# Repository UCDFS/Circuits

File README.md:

# UCDFS Circuits Repository

Welcome to the University College Dublin Formula Student (UCDFS) KiCad circuits repository! This is the central location for all our electronic circuit designs, schematics, and PCB layouts.

## About

This repository contains KiCad project files for various electronic circuits used in our Formula Student vehicle and projects. All designs are created using KiCad, an open-source electronic design automation (EDA) suite.

## Getting Started

1. **Clone this repository:**
   ```bash
   git clone https://github.com/UCDFS/Circuits.git
   cd Circuits
   ```

2. **Open a project in KiCad:**
   - Launch KiCad
   - Open the `.kicad_pro` file for the project you want to work on
   - The schematic (`.kicad_sch`) and PCB layout (`.kicad_pcb`) will be accessible from the project manager

3. **View/Edit Schematics:**
   - Click "Schematic Editor" in KiCad's main window
   - Or directly open the `.kicad_sch` file

4. **View/Edit PCB Layout:**
   - Click "PCB Editor" in KiCad's main window
   - Or directly open the `.kicad_pcb` file

## Repository Structure

```
├── README.md                     # This file
├── .gitignore                    # Git ignore rules for KiCad projects
└── [Project Name]/               # Individual circuit projects
    ├── [Project].kicad_pro       # KiCad project file
    ├── [Project].kicad_sch       # Schematic file
    └── [Project].kicad_pcb       # PCB layout file
```

## Contributing

When contributing new circuits or modifications:

1. **Create a new branch** for your work
2. **Organize projects** in clearly named directories
3. **Follow naming conventions:** Use descriptive names for projects and files
4. **Include all necessary files:** Ensure `.kicad_pro`, `.kicad_sch`, and `.kicad_pcb` files are included
5. **Document your work:** Add project details to a README in each circuit subfolder

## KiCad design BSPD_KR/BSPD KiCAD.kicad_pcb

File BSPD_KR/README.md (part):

# BSPD: Brake System Plausibility Device

This folder holds the KiCad design for the car's BSPD board. The original design is by Nebojša Cvetković, later updated by Keelan Reilly (hence the `_KR` in the folder name). It was reworked in September and October 2026: first to fix three rule and reliability problems, then so that a faulty or unplugged sensor trips the BSPD on its own.

> **Status (8 October 2026):** the design passes KiCad's checks and behaves correctly in simulation, including the sensor-fault tests. **No board has been built or bench-tested yet.** Read [section 5](#5-open-issues-read-before-ordering) before ordering. [Issue 1](#issue-1-the-current-sensor-must-stay-below-474-v-in-normal-driving) needs an answer from the team first.

## The short version of what changed

**September 2026 (the latch rework):**

1. **The old board reset itself too early.** After tripping, it closed the shutdown circuit again by itself after roughly 7 to 14 seconds, depending on part tolerances. FSUK rule T11.6.1 only allows a self-reset after more than 10 seconds. The new board stays tripped until the LV master switch (LVMS) is turned off and on again.
2. **The old board was too slow to trip.** Its "500 ms" timer actually took about 0.51 s with exactly nominal parts, which is over the limit in T11.6.2. The new timer takes about 0.36 s (0.29 s to 0.43 s across part tolerances).
3. **One capacitor was drawn backwards.** C10 is an electrolytic capacitor, so it has a + leg and a − leg. Its + leg was connected to ground. That is fixed.

**October 2026 (sensor faults):**

4. **A single unplugged or faulty sensor now trips the BSPD.** Before, an unplugged brake sensor looked to the board like "braking hard", and an unplugged current sensor looked like "high power". The board then waited for the other condition before doing anything. Now, any sensor reading below 0.24 V (wire broken, connector unplugged, short to ground) or above 4.74 V (short to the sensor's 5 V supply) trips the BSPD after about 0.16 s. The trip is latched like any other. This is what rule T11.9.2 asks for.
5. **The "sensor missing" level moved from 0.45 V to 0.24 V.** The brake sensors output 0.5 V at rest, so the old level left only 0.05 V of margin, and a healthy sensor could have read as missing.

The PCB, BOMs, manufacturing files and 3D model were all updated to match. [Section 4](#4-exactly-what-changed) lists every change.

## Contents

1. [What a BSPD is and why the car needs one](#1-what-a-bspd-is-and-why-the-car-needs-one)
2. [Background you need](#2-background-you-need)
3. [How this board works, stage by stage](#3-how-this-board-works-stage-by-stage)
4. [Exactly what changed](#4-exactly-what-changed)
5. [Open issues: read before ordering](#5-open-issues-read-before-ordering)
6. [Calibrating and bench-testing a new board](#6-calibrating-and-bench-testing-a-new-board)
7. [Files in this folder and how to regenerate them](#7-files-in-this-folder-and-how-to-regenerate-them)
8. [Glossary](#8-glossary)

---

## 1. What a BSPD is and why the car needs one

### The shutdown circuit

The car has a **shutdown circuit (SDC)**. It is one long loop of wire that passes through every safety device on the car: the shutdown buttons, the inertia switch, the brake over-travel switch, the IMD, the AMS, this board, and others. Current flows round the loop and holds the **AIRs** (accumulator isolation relays) closed. The AIRs are the big relays that connect the high-voltage battery to the rest of the car.

If any device in the loop opens its contact, current stops flowing round the loop, the AIRs drop open, and the high-voltage battery is disconnected. The car stops making power.

### What the BSPD is looking for

The BSPD is one of the devices in that loop. It watches for one dangerous situation:

> **The driver is braking hard while the motor is still being given a lot of power.**

That never happens in normal driving. If it does, something is broken. The throttle might be stuck, a pedal sensor might have failed, or there might be a bug in the VCU software. The BSPD does not try to work out which. It just opens the shutdown circuit.

It also has to notice when one of its own sensors fails. A broken sensor wire could otherwise blind it without anyone knowing.

It is deliberately built without any microcontroller or code. The BSPD is the backstop for software failures, so if it ran software, the same kind of bug it is meant to catch could also disable it.

### What the rules require (FSUK 2026, sections T11.6 and T11.9)

| Rule | What it says | How this board meets it |
|---|---|---|
| T11.6.1 | Must be a standalone, non-programmable circuit. Must open the SDC when hard braking happens while at least 5 kW is going to the motors. Then it must either stay open until the LVMS is power-cycled, or reset itself only after the condition has been gone for more than 10 s. | Comparators and logic gates detect the condition, and a latch keeps the SDC open until power-cycle. There is no software anywhere on the board. |
| T11.6.2 | Must open the SDC if the implausibility lasts more than 500 ms. | An RC timer trips it after about 0.36 s. |
| T11.6.3 | Must be powered directly from the LVMS. | Power comes in on J3. That must be wired straight from the LVMS. |
| T11.6.4 | No extra functions on the board. Only power, the required sensors and the shutdown circuit connect to it. | The only connectors are J1 (sensors), J2 (shutdown circuit) and J3 (power). |
| T11.6.5 | Hard braking must be measured with a brake pressure sensor. The threshold must be 30 bar or less, and below the point where the wheels lock. | There are two pressure inputs (front and rear), each with its own adjustable threshold. |
| T11.6.6 | Power must be measured with a DC current sensor. The threshold must equal 5 kW at the maximum TS voltage. | There is one current input with an adjustable threshold. |
| T11.6.7 | It must be possible to disconnect each sensor wire separately at inspection. | Every sensor comes in through connector J1. Unplugging any one of them trips the BSPD within about 0.16 s. |
| T11.6.8, T11.9.2, T11.9.5 | The sensor signals are System Critical Signals. An open circuit, a short to ground, or (for analogue sensors) a short to the supply voltage must put the system into its safe state, which for the BSPD is an open shutdown circuit. | Six "sensor fault" comparators watch the three sensors for readings below 0.24 V or above 4.74 V and trip the latch ([stage 5](#stage-5-sensor-fault-detection)). |
| T11.6.9, IN4.1.3 | At inspection, the team proves the BSPD works by injecting a fake current signal (equivalent to 5 kW) while pressing the brake pedal. | See [section 6](#6-calibrating-and-bench-testing-a-new-board). |

The full rules PDF is at the root of this repository.

---

## 2. Background you need

Every idea in this section is used in section 3. Skip any you already know.

### Voltage and ground

Voltage is always measured between two points. When we say a wire is "at 5 V", we mean 5 V above **ground**, the shared reference wire. On this board ground is called **GLV−**. One part of the schematic labels it **GND** instead, but KiCad joins the two names, and they are the same wire.

### The two supplies on this board

- **GLV+** is the car's low-voltage supply. It comes in on J3. It powers the relay coil (a 12 V part) and all four comparator chips.
- **+5V** is made on the board from GLV+ by **U4**, an LM7805 voltage regulator. A regulator takes in a higher voltage that may wobble and puts out a steady fixed voltage. Everything that does logic runs from +5V, and so do all the reference voltages.

### Resistors and voltage dividers

Put two resistors in series between +5V and ground, and the point between them sits at a fixed fraction of 5 V:

```
V_middle = 5 V × R_bottom / (R_top + R_bottom)
```

This board uses dividers to make fixed **reference voltages** that signals get compared against. For example, R7 (100 kΩ, on top) and R8 (5.1 kΩ, on the bottom) give 5 × 5.1 / 105.1 = **0.24 V**.

A **potentiometer** (RV1, RV2, RV3) is an adjustable divider. Turning its screw moves the middle pin (the "wiper") anywhere between 0 V and 5 V. These three set the trip thresholds. They are 25-turn trimmers, so each one takes many turns to go from end to end. That makes them easy to set accurately.

### Pull-up and pull-down resistors

A wire that isn't connected to anything is "floating". Its voltage is undefined, and it picks up electrical noise. A **pull-down** resistor (to ground) or a **pull-up** resistor (to +5V) gives the wire a default voltage that anything stronger can override.

- R1, R2 and R3 (100 kΩ) pull each sensor input down to 0 V. An unplugged sensor therefore reads 0 V instead of random noise. This is what lets the board detect an unplugged sensor.
- R13, R14, R15, R26, R27 and R31 (10 kΩ) pull comparator outputs up to 5 V. The next part explains why those are needed.

### Comparators (U5, U19, U22, U23)

A comparator has two inputs, marked **+** and **−**. It answers one question: **is the + input higher than the − input?** U5 and U19 (LM339) each hold four separate comparators, labelled A, B, C and D in the schematic. U22 and U23 (LM393) are the same kind of comparator, with two per chip, labelled A and B.

All of them have what is called an **open-collector output**. This confuses everyone at first, so here it is slowly:

- If **+ is higher than −**, the output lets go of its wire. The pull-up resistor then pulls the wire up to 5 V. **Output = HIGH.**
- If **− is higher than +**, the output connects its wire to ground. **Output = LOW.**

Because an open-collector output can only ever pull *down*, several outputs can safely be joined onto the same wire. If **any** of them pulls low, the wire goes low. This is called a **wired-OR**. This board uses it twice: six fault comparators share one `FAULT_N` wire, and two comparators share the `TRIP_REQ_N` wire.

### Active-low signals

A signal is **active-low** if LOW means "yes, this is happening". Most comparator outputs on this board are active-low: the wire goes LOW when the brake is pressed hard, when the current is high, or when a sensor is faulty. Names ending in `_N` (like `FAULT_N` and `TRIP_REQ_N`) follow this convention. It is the main thing that makes the logic look backwards.

### Logic gates

Logic chips treat a voltage near 5 V as **1 (HIGH)** and a voltage near 0 V as **0 (LOW)**. Each logic chip on this board is a tiny 5-pin package holding exactly one gate.

| Gate | Chips | The output is HIGH when… |
|---|---|---|
| NOT (inverter) | U9 (SN74LVC1G04) | the input is LOW |
| AND | U18 (SN74AHCT1G08) | both inputs are HIGH |
| NOR | U6, U20, U21 (SN74AHC1G02) | both inputs are LOW |

### Capacitors, RC timers and debouncing

A capacitor stores charge. If you charge (or drain) it through a resistor, its voltage changes gradually rather than instantly. How fast it changes depends on the **time constant**, written τ (the Greek letter tau):

```
τ = R × C
charging: V(t) = V_supply × (1 − e^(−t/τ))      draining: V(t) = V_start × e^(−t/τ)
```

After one τ the capacitor has covered 63% of the distance. Add a comparator watching the capacitor's voltage and you have a **timer**. It answers the question "has this input been on for longer than X?"

The same trick with a shorter time is called **debouncing**. It means ignoring blips that are too short to matter, like a connector that loses contact for a few milliseconds over a bump. This board uses a 0.36 s timer for the brake-plus-power check and a 0.16 s debounce for sensor faults.

**Electrolytic capacitors** (C10 and C13 here, both 10 µF) store a lot of charge for their size, but they are **polarised**. One leg is + and must always be at the higher voltage. Fitted backwards, they leak, heat up, and can eventually fail or burst. On this PCB, the + pad of each one is the square pad, and it is marked with + on the silkscreen.

The small ceramic capacitors are not polarised. Most (0.1 µF: C5, C6, C7, C8, C9, C12, C14 and C16; 0.22 µF: C4) sit right next to a chip's power pins as **decoupling** capacitors. Each one is a tiny local reservoir that smooths out the current spikes a chip draws every time it switches. C15 (1 µF) is different: it is the debounce capacitor for sensor faults.

### Chip packages: DIP and SOIC

Most chips on this board are **DIP** (through-hole) parts, with two rows of legs that go through holes in the board. U22 and U23 are **SOIC-8** surface-mount parts. They are much smaller and are soldered flat onto pads on the **bottom** of the board. Each one sits in the empty space between the two rows of legs of a DIP chip (U5 and U19), because that is where its connections are.

### The SR latch (a one-bit memory)

Take two NOR gates and connect each gate's output to one input of the other. The result *remembers* things. It has two control inputs:

- **S (set):** a brief HIGH here puts it into the "tripped" state.
- **R (reset):** a brief HIGH here puts it back into the "OK" state.

When both inputs are LOW, it stays in whatever state it was last put in, for as long as it has power. That is exactly the behaviour "stay open until power-cycled" needs.

### A MOSFET used as a switch (Q1, 2N7002)

A MOSFET is a switch controlled by a voltage. Q1 is an N-channel MOSFET wired as a **low-side switch**. When its gate (control pin) is at 5 V, it conducts and connects the bottom of the relay coil to ground. When its gate is at 0 V, it is off.

### The relay and its flyback diode (K1 and D9)

A relay is a switch moved by an electromagnet. Current through its **coil** pulls its contacts together. K1 is a **normally open** relay: with no coil current, the contacts are apart. Those contacts sit in the shutdown circuit, through connector J2. So:

> **Relay powered = shutdown circuit closed = car can drive.**
> **Relay unpowered = shutdown circuit open = car is shut down.**

This arrangement is **fail-safe**. If the board loses power, a wire breaks, or a chip dies with its output stuck low, the relay drops out and the car shuts down.

When the current through a coil is switched off, the coil's collapsing magnetic field produces a voltage spike big enough to destroy Q1. **D9** (a 1N4001 diode) sits across the coil and gives that energy a safe path. This is called a **flyback diode**.

---

## 3. How this board works, stage by stage

### The main path: brake plus power

```
 CURRENT_SENSOR (J1 pin 3)      BRAKE_SENSOR_FRONT (J1 pin 1)     BRAKE_SENSOR_REAR (J1 pin 2)
           │                                │                                  │
 Stage 1   │  input protection (1 kΩ in series, 100 kΩ pull-down, test point)  │
           │                                │                                  │
 Stage 2   U5A                              U19A                               U19C
           "current too high"               "front pressure too high"          "rear pressure too high"
           LOW = yes  (LED1)                LOW = yes  (LED2)                  LOW = yes  (LED3)
           │                                └────────────────┬─────────────────┘
           │                                        Stage 3a: U18 AND
           │                                        "either brake pressed hard", LOW = yes
           └──────────────────────┬──────────────────────────┘
                         Stage 3b: U6 NOR
                         IMPLAUSIBLE: HIGH = hard braking AND high power, right now
                                  │
                         Stage 4: R20 + C10 timer, watched by U5C
                         "implausible for longer than ~0.36 s"
                                  │
                         TRIP_REQ_N  (LOW = trip, please; LED4)  ◄──── Stage 5: sensor faults (below)
                                  │
                         U9 NOT  →  BSPD_TRIP  (HIGH = trip now)
                                  │
                         Stage 6: U20 + U21 latch  →  LATCH_Q  (HIGH = tripped, remembered)
                                  │      ↑ POR (C13, R30, D10) forces it to "OK" at power-up
                                  │
                         Stage 7: U5D  →  Q1  →  K1 relay  →  J2  →  shutdown circuit
                         tripped: relay off, shutdown circuit open  (LED5)
```

### The fault path: is each sensor healthy?

```
 each sensor ──► "reading below 0.24 V?"  U5B (current), U19B (front), U19D (rear)  ──┐
          └────► "reading above 4.74 V?"  U22A (current), U23A (front), U23B (rear) ─┤  all six outputs joined:
                                                                                     │  FAULT_N (LOW = a sensor is faulty)
                                                                                     ▼
                                               R32 + C15 debounce (~0.16 s), watched by U22B
                                                                                     │
                                                                                     ▼
                                               pulls TRIP_REQ_N LOW  →  same latch and relay as a real trip
```

Many wires in the schematic have no name, and KiCad numbers them automatically (`Net-(U6-…)` and similar). The descriptions below name each wire by what it does and by the pins it joins.

### Stage 0: Power

| Part | Job |
|---|---|
| J3 | Power input. Pin 1 is GLV+ and pin 2 is GLV−. It must be supplied directly from the LVMS (T11.6.3). |
| U4 (LM7805) | Makes +5V from GLV+. |
| C4 (0.22 µF) | Input capacitor for U4, on GLV+. |
| C7, C12 (0.1 µF) | On GLV+. Decoupling for the comparator chips U5 and U19, which run directly from GLV+ (pin 3 on each). C7 also serves U22, which sits inside U5's footprint and takes its power straight from U5's supply pins. |
| C16 (0.1 µF) | On GLV+. Decoupling for U23. |
| C5, C6, C8, C9 (0.1 µF) | On +5V. Output capacitor for U4, and decoupling for the logic gates U6, U9 and U18. |
| C14 (0.1 µF) | On +5V. Decoupling for the two latch chips, U20 and U21. |

The comparators run from GLV+, but they only ever see 0 to 5 V on their inputs, which is well within what they accept. Their outputs are pulled up to +5V, so the logic chips also only ever see 0 to 5 V.

### Stage 1: Sensor inputs

| Signal | J1 pin | Series resistor | Pull-down | Test point (live signal) | Net name after the 1 kΩ |
|---|---|---|---|---|---|
| BRAKE_SENSOR_FRONT | 1 | R5, 1 kΩ | R2, 100 kΩ | TP2 | `SENS_FRONT` |
| BRAKE_SENSOR_REAR | 2 | R6, 1 kΩ | R3, 100 kΩ | TP3 | `SENS_REAR` |
| CURRENT_SENSOR | 3 | R4, 1 kΩ | R1, 100 kΩ | TP1 | `SENS_CUR` |

The 1 kΩ series resistors limit the current into the comparator inputs if a wire picks up a spike or gets shorted to something. The 100 kΩ pull-downs make an unplugged sensor read 0 V.

J1 carries only the three signal wires. The sensors get their power and ground from elsewhere in the car's wiring.

**What the sensors output.**
- The brake sensors are TE M7139-500PG transducers: 0.5 V at 0 bar, rising to 4.5 V at 500 psi (34.5 bar).
- The current sensor is the Orion BMS Hall-effect sensor: 2.5 V at 0 A, changing by 10 mV per amp.
- So a healthy sensor always reads somewhere between 0.5 V and 4.5 V. That is what makes it possible to treat anything outside that band as a fault.

### Stage 2: "Too high" comparators

Each sensor has one comparator that asks "is the signal above its threshold?" The sensor goes into the **−** input and the adjustable threshold (from a potentiometer) goes into the **+** input. When the signal rises above the threshold, − is higher than +, so the output pulls LOW.

| Sensor | Comparator (− pin, + pin, output pin) | Threshold set by / measured at | Output pull-up | LED (via resistor) |
|---|---|---|---|---|
| Current | U5A (4, 5, 2) | RV1 / TP4 | R13 | LED1 (R16) |
| Front brake | U19A (4, 5, 2) | RV2 / TP5 | R14 | LED2 (R17) |
| Rear brake | U19C (10, 11, 13) | RV3 / TP6 | R15 | LED3 (R18) |

Each LED has its + leg (anode) on +5V and its − leg (cathode) going through a 10 kΩ resistor to the comparator output wire. The LED lights when that wire goes LOW.

### Stage 3: Combining the signals

**U18, an AND gate**, takes the front-brake wire and the rear-brake wire. Its output is HIGH only when both brake wires are HIGH, meaning neither brake is pressed hard. If either one goes LOW, U18's output goes LOW. So U18's output is an active-low "**either brake pressed hard**" signal.

**U6, a NOR gate**, takes the current wire and U18's output. Its output is HIGH only when both inputs are LOW:

| Current wire | Brake wire (from U18) | U6 output | Meaning |
|---|---|---|---|
| HIGH (current OK) | HIGH (brakes OK) | LOW | Normal driving |
| LOW (current high) | HIGH (brakes OK) | LOW | Accelerating, which is fine |
| HIGH (current OK) | LOW (braking hard) | LOW | Braking, which is fine |
| **LOW (current high)** | **LOW (braking hard)** | **HIGH** | **Implausible: braking hard with power on** |

U6's output is the **IMPLAUSIBLE** signal. It is HIGH whenever the dangerous combination is happening at that instant.

### Stage 4: The 500 ms timer

The rules give the car up to 500 ms of implausibility before the BSPD must act. That allows for things like the driver stabbing the brake for a moment while lifting off the throttle.

- U6's output feeds **R20 (39 kΩ)**, which charges **C10 (10 µF)**. The wire between them is the net called `500ms`.
- When IMPLAUSIBLE is HIGH, C10 charges towards 5 V with τ = 39 kΩ × 10 µF = **0.39 s**.
- **U5C** compares C10's voltage (− input, pin 10) against a fixed **3.0 V** (+ input, pin 11). The 3.0 V comes from the R22 (10 kΩ) and R23 (15 kΩ) divider: 5 × 15 / 25 = 3.0 V.
- C10 reaches 3.0 V after t = τ × ln(5 / (5 − 3)) = 0.39 × 0.916 = **0.36 s**.
- At that point U5C's output (pin 13) pulls the `TRIP_REQ_N` wire LOW and LED4 lights (through R28). **U9** inverts that, so its output, **BSPD_TRIP**, goes HIGH.
- If IMPLAUSIBLE goes away before 0.36 s, U6's output goes LOW and C10 drains back out through R20. A short blip is ignored.
- Electrolytic capacitors are only accurate to ±20%, so C10 is really somewhere between 8 µF and 12 µF. That puts the trip time between **0.29 s and 0.43 s**, always under the 500 ms limit.
- If a second implausibility comes shortly after a first one, C10 may not have fully drained yet, so the second trip comes a little sooner. That is the safe direction.

### Stage 5: Sensor fault detection

Every sensor is checked for two kinds of fault:

- **Reading too low (below 0.24 V):** the wire is broken, the connector is unplugged, or the signal is shorted to ground. All three read close to 0 V, because the 100 kΩ pull-down takes over.
- **Reading too high (above 4.74 V):** the signal is shorted to the sensor's 5 V supply.

A healthy sensor never reads outside 0.5 V to 4.5 V, so each limit sits roughly halfway between "healthy" and "faulty".

| Sensor | "Too low" comparator (+ = sensor, − = 0.24 V) | 0.24 V reference | "Too high" comparator (− = sensor, + = 4.74 V) | 4.74 V reference |
|---|---|---|---|---|
| Current | U5B (+ 7, − 6, out 1) | R7 100 kΩ / R8 5.1 kΩ | U22A (− 2, + 3, out 1) | R33 1 kΩ / R34 18 kΩ (`OVR_REF_CUR`) |
| Front brake | U19B (+ 7, − 6, out 1) | R9 100 kΩ / R10 5.1 kΩ | U23A (− 2, + 3, out 1) | R35 1 kΩ / R36 18 kΩ (`OVR_REF_BRK`) |
| Rear brake | U19D (+ 9, − 8, out 14) | R11 100 kΩ / R12 5.1 kΩ | U23B (− 6, + 5, out 7) | R35 / R36 (`OVR_REF_BRK`, shared) |

The references work out like this:
- 0.24 V = 5 V × 5.1 / 105.1
- 4.74 V = 5 V × 18 / 19

The comparators are wired so that a fault always pulls the output LOW. For "too low", the sensor goes to +, so when it drops under the reference, − is higher. For "too high", the sensor goes to −.

**All six outputs are joined onto one wire, `FAULT_N`**, which **R31 (10 kΩ)** pulls up to 5 V. If any sensor is faulty, `FAULT_N` goes LOW.

**Debounce.** `FAULT_N` feeds **R32 (100 kΩ)**, which charges **C15 (1 µF)**. The wire between them is `FAULT_F`.
- Normally C15 sits at 5 V. When `FAULT_N` goes LOW, C15 drains through R32 with τ = 100 kΩ × 1 µF = **0.1 s**.
- **U22B** compares `FAULT_F` (+ input, pin 5) with the 1.02 V reference `REF_1V0` (− input, pin 6). That is the same reference U5D uses, made by R24 and R25.
- C15 falls below 1.02 V after about 0.1 × ln(5 / 1.02) ≈ **0.16 s** (0.14 s to 0.18 s with C15's ±10% tolerance).
- At that point U22B's output (pin 7) pulls **`TRIP_REQ_N`** LOW. That is the very same wire the 500 ms timer uses, so from here a sensor fault is handled exactly like a real trip: U9 → BSPD_TRIP → latch → relay opens. LED4 and then LED5 light.
- A blip shorter than about 0.12 s doesn't drain C15 far enough to matter, so a connector that loses contact for a moment over a bump does not trip the car.

**At power-up**, C15 starts empty, so for the first ~25 ms the debounce output says "fault". The power-on reset (stage 6) holds the latch in "OK" for far longer than that, so this does nothing. Sensors that come alive a little after the board are also fine, as long as they are valid before the power-on reset lets go (at least ~0.36 s; simulated with sensors 0.2 s late).

**Where the new chips are.**
- U22 sits on the bottom of the board, inside U5's footprint. U5's pins carry almost everything it needs: `SENS_CUR`, `REF_1V0`, `TRIP_REQ_N`, `FAULT_N` (U5 pin 1) and power.
- U23 sits on the bottom inside U19's footprint, for the same reason: `SENS_FRONT`, `SENS_REAR`, `FAULT_N` (U19 pins 1 and 14) and power.
- U23 has its own decoupling capacitor, C16. U22 shares U5's supply pins and U5's capacitor C7.

### Stage 6: The latch

**U20 and U21** are two NOR gates wired as an SR latch:

- **U21:** inputs `LATCH_Q` and `BSPD_TRIP`, output `LATCH_QN`
- **U20:** inputs `LATCH_QN` and `POR`, output `LATCH_Q`

BSPD_TRIP is the **set** input and POR is the **reset** input. LATCH_Q is HIGH when the BSPD is tripped.

Here is what happens during a trip:

1. Normally LATCH_Q = 0 and LATCH_QN = 1.
2. BSPD_TRIP goes HIGH. U21 now has a HIGH input, so its output, LATCH_QN, goes to 0.
3. U20 now sees LATCH_QN = 0 and POR = 0. Both inputs are LOW, so its output, LATCH_Q, goes to 1.
4. U21 now sees LATCH_Q = 1, so LATCH_QN stays 0 even after BSPD_TRIP goes LOW again. **The latch is locked in the tripped state.**

There are only two ways out: POR going HIGH (which happens at power-up), or losing the 5 V supply altogether. In practice, both mean turning the LVMS off and on.

#### The power-on reset (POR): C13, R30 and D10

When a latch first gets power, it lands in a random state. Without help, the car would sometimes power up already tripped. The POR circuit forces the latch into "OK" for a moment every time power comes on.

- **C13 (10 µF)** connects +5V to the `POR` wire. **R30 (100 kΩ)** connects `POR` to ground.
- When power comes on, +5V jumps up. C13 starts out empty, so it drags `POR` up to about 5 V along with it.
- C13 then charges through R30, and `POR` falls back towards 0 V with τ = 100 kΩ × 10 µF = **1 s**.
- The latch chip reads POR as HIGH (reset active) until it falls below about 3.5 V, which takes about 0.36 s. It reads POR as definitely LOW once it falls below about 1.5 V, which takes about 1.2 s. During that window the latch is held in "OK".
- **D10 (1N4148)** matters at power-off. When +5V drops, C13 would try to push `POR` below 0 V, which can damage U20's input. D10 stops it going much below −0.6 V and empties C13 quickly, so a quick off-and-on still gives a clean reset.
- If a real fault is present at power-up, nothing goes wrong. The trip request is still there when POR lets go, so the latch sets as soon as the reset ends.

### Stage 7: Driving the relay

- **U5D** compares LATCH_Q (− input, pin 8) against the fixed **1.02 V** `REF_1V0` (+ input, pin 9). That reference comes from the R24 (39 kΩ) and R25 (10 kΩ) divider: 5 × 10 / 49 = 1.02 V. U5D is just acting as an inverter: when LATCH_Q is HIGH (tripped), its output (pin 14) pulls LOW.
- Pin 14's wire is **Q1's gate**, pulled up to +5V by R27 (10 kΩ).
- **Not tripped:** R27 holds Q1's gate at 5 V, so Q1 conducts. Current flows from GLV+ through K1's coil and Q1 to ground. The relay is closed, so the shutdown circuit is closed through J2.
- **Tripped:** U5D pulls Q1's gate LOW, so Q1 turns off and the coil current stops. K1 opens, the shutdown circuit opens, the AIRs open, and the high voltage is disconnected. LED5 lights (through R29).
- **J2** connects to the shutdown circuit. Pin 1 is BSPD_Shutdown+ and pin 2 is BSPD_Shutdown−.

Why does a comparator drive Q1, rather than the latch driving it directly? On the old board, U5D watched the 10-second reset timer. Reusing it kept the PCB changes small, and it also makes a convenient 5 V gate driver.

### What the LEDs mean

All five LEDs are green. They run at only about 0.3 mA, so they are dim, especially in daylight.

| LED | When it is on |
|---|---|
| LED1 | The current is above its threshold. |
| LED2 | The front brake pressure is above its threshold. |
| LED3 | The rear brake pressure is above its threshold. |
| LED4 | **A trip is being requested:** either the implausibility has lasted at least ~0.36 s, or a sensor has been faulty for at least ~0.16 s. It goes off again once the cause clears. |
| LED5 | **The BSPD has tripped and latched.** The relay and the shutdown circuit are open. It stays on until the LVMS is power-cycled. |

There is no separate "sensor fault" LED; there was no room on the top of the board. If LED5 is on but LED1, LED2 and LED3 are all off, a sensor fault is the likely cause. Check TP1, TP2 and TP3 with a meter.

### Test points

Measure all of these against GLV− (ground).

| Test point | What it measures |
|---|---|
| TP1 | The current sensor signal |
| TP2 | The front brake sensor signal |
| TP3 | The rear brake sensor signal |
| TP4 | The current threshold, set with RV1 |
| TP5 | The front brake threshold, set with RV2 |
| TP6 | The rear brake threshold, set with RV3 |

---

## 4. Exactly what changed

This section compares the current design with the version on GitHub `main` as of Keelan's last commit there (`f4da82b`, 9 July 2026). The work came in two batches: **A** (September, the latch rework) and **B** (October, sensor faults).

### 4.1 Behaviour before and after

| | Before | After |
|---|---|---|
| Time from implausibility to trip | ~0.51 s with nominal parts (0.41–0.62 s across tolerances). **Over the 500 ms limit.** | ~0.36 s with nominal parts (0.29–0.43 s across tolerances). |
| What happens after a trip | Resets itself roughly 7–14 s after the condition clears. **Can be under the 10 s the rules require.** | Stays tripped until the LVMS is power-cycled. |
| C10 | Fitted backwards, so it was reverse-biased (by up to 5 V) whenever an implausibility happened. | Fitted the right way round. |
| Power-up | The relay stayed open for about 16 s after every power-up. C11 connected +5V to the 10-second node, so switching on dragged that node to 5 V, and it then had to drain through R21 like a trip. Confirmed in simulation. | The POR circuit forces the latch to "OK", so the relay closes within a few milliseconds of power-up. |
| One sensor unplugged, or shorted to ground | **Did not trip.** The board treated it as "braking hard" or "high power" and waited for the other condition. | Trips after ~0.16 s and stays tripped. |
| One sensor shorted to its 5 V supply | **Did not trip**, for the same reason. | Trips after ~0.16 s and stays tripped. |
| "Sensor missing" level | 0.45 V, only 0.05 V below a brake sensor's resting 0.5 V. | 0.24 V. |

### 4.2 Batch A: the latch rework (September 2026)

**Schematic: removed (the old 10-second self-reset timer)**

| Ref | Part | What it did |
|---|---|---|
| Q3 | 2N7002 MOSFET | When the BSPD tripped, it charged up the 10-second node from +5V. |
| R19 | 1 kΩ | Series resistor between Q3 and the 10-second node. |
| C11 | 10 µF electrolytic | The 10-second capacitor, between +5V and the `10s` net. |
| R21 | 1 MΩ | Slowly drained the 10-second node. τ = 1 MΩ × 10 µF = 10 s. |

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
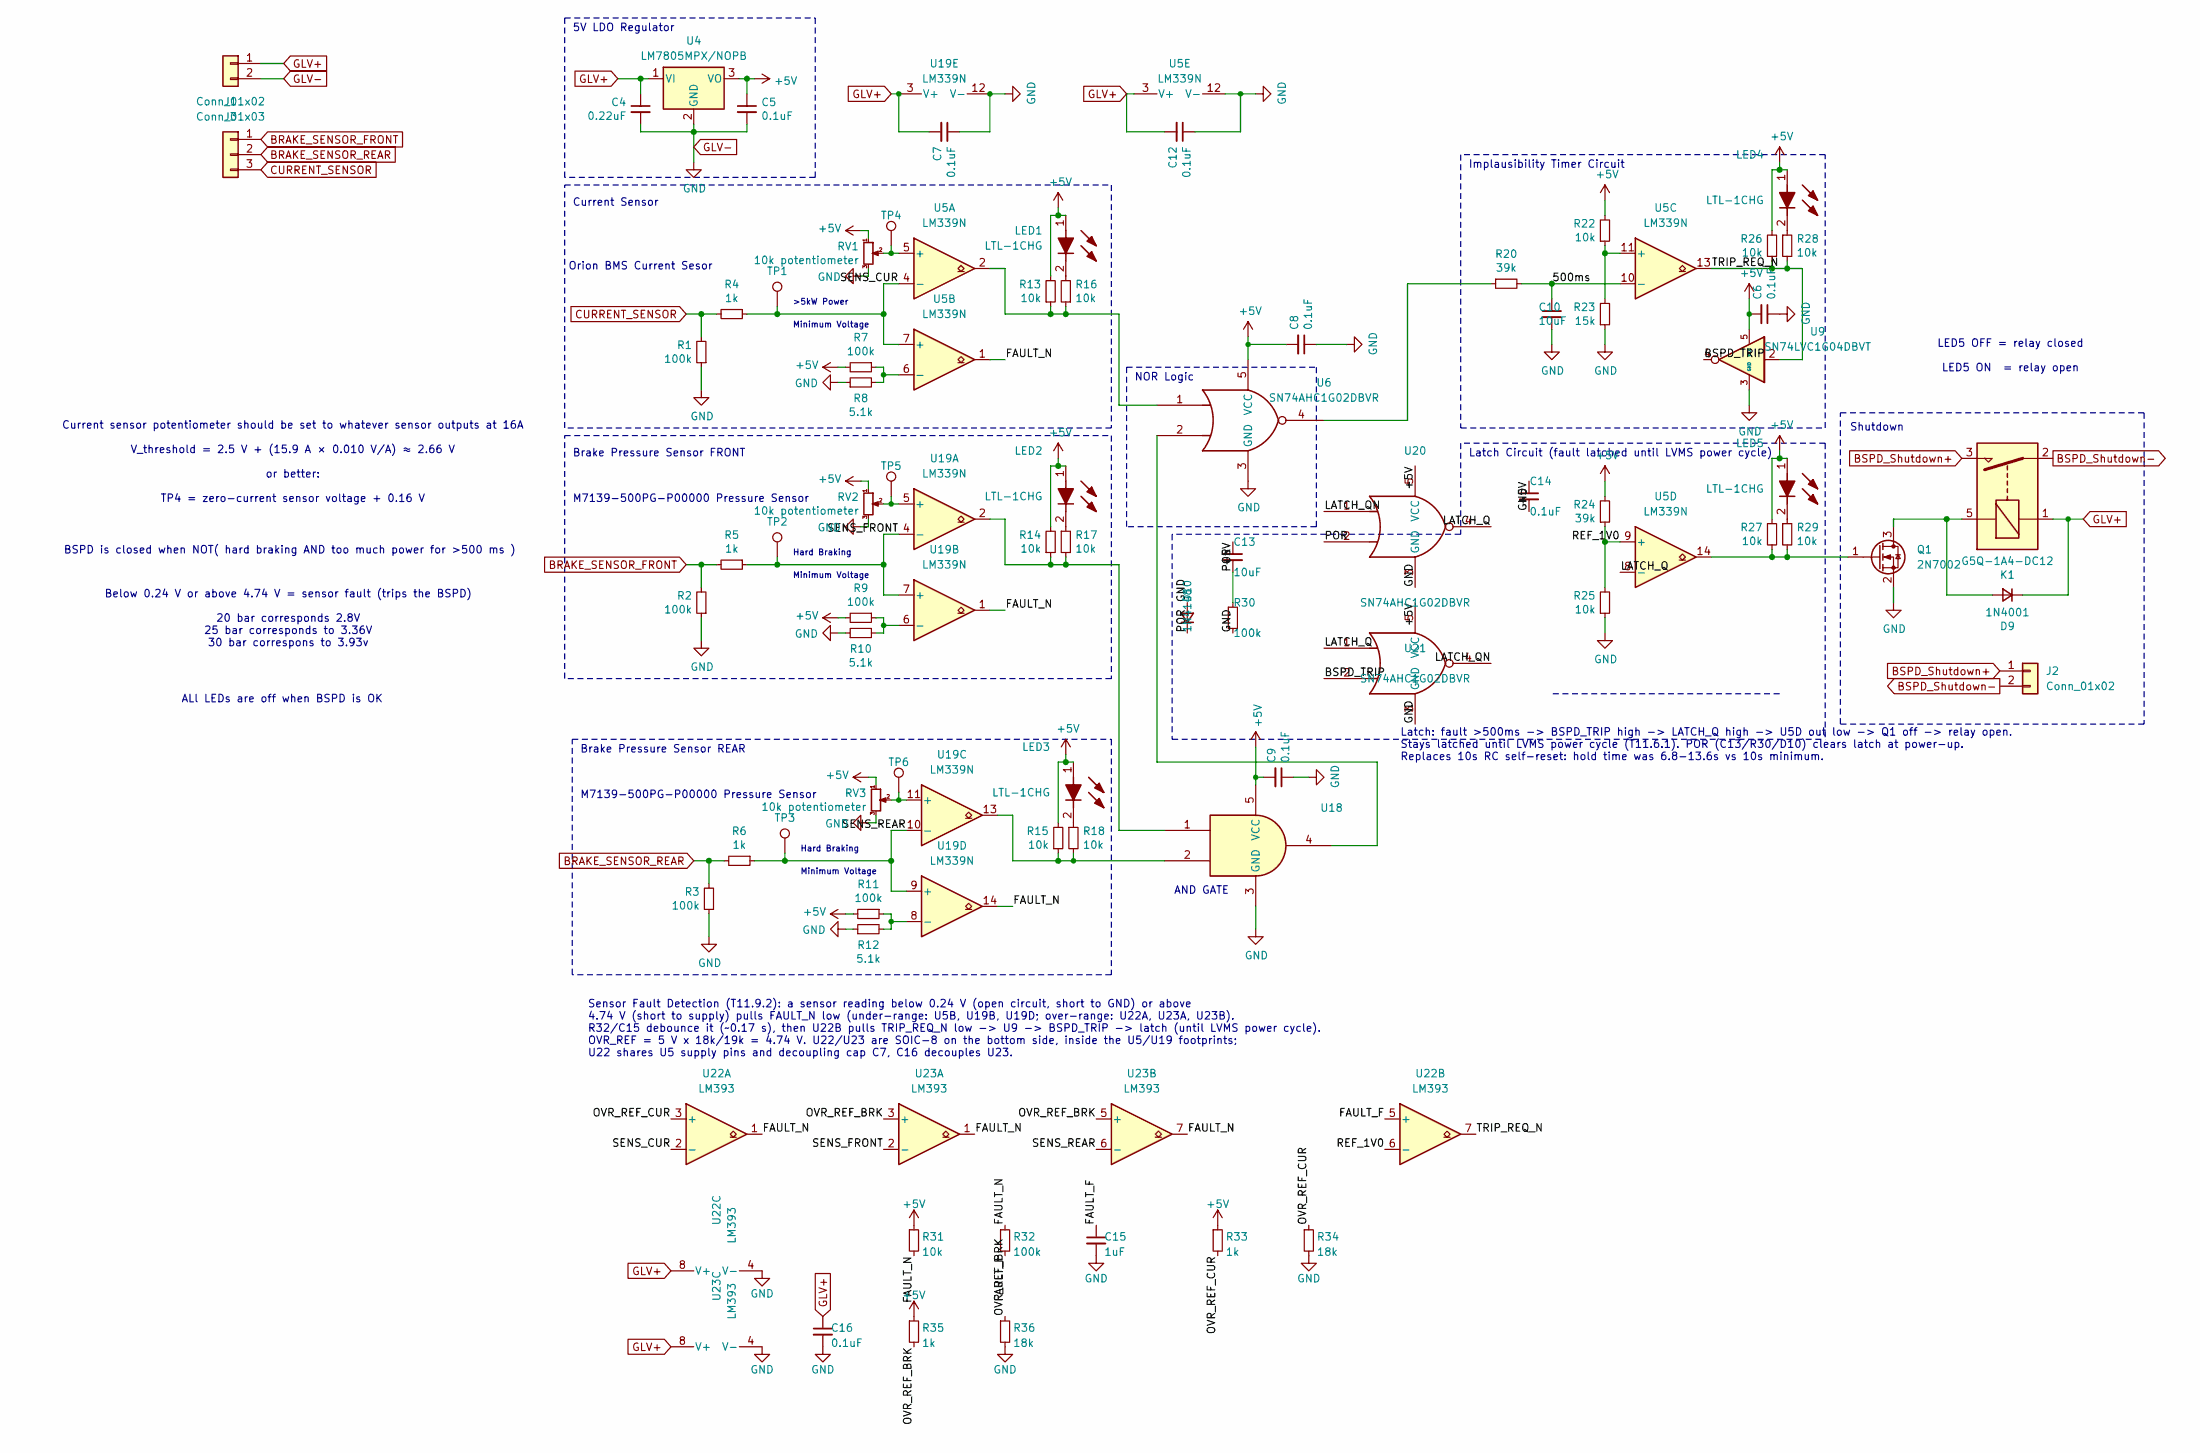
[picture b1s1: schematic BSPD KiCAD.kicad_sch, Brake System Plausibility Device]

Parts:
C4: 0.22uF; FA14X7R1H224KNU00; Part Number FA14X7R1H224KNU00
C5, C6, C7, C8, C9, C12, C14: 0.1uF; FA18X7R1H104KNU00; Part Number FA18X7R1H104KNU00
C10, C13: 10uF; CP_Radial_D5.0mm_P2.50mm; Part Number ECE-A1EKA100I
C15: 1uF; C_0805_2012Metric; Part Number CL21B105KBFNNNE
C16: 0.1uF; C_0805_2012Metric; Part Number CL21B104KBCNNNC
D9: 1N4001; D_DO-41_SOD81_P10.16mm_Horizontal; Manufacturer Part Number 1N4001
D10: 1N4148; D_DO-41_SOD81_P10.16mm_Horizontal; Part Number 1N4148
J1: Conn_01x03; JST_XH_B3B-XH-A_1x03_P2.50mm_Vertical; Part Number B3B-XH-A
J2, J3: Conn_01x02; JST_XH_B2B-XH-A_1x02_P2.50mm_Vertical; Part Number B2B-XH-A
K1: G5Q-1A4-DC12; Relay_SPST_Omron-G5Q-1A; Part Number G5Q-1A4-DC12
LED1, LED2, LED3, LED4, LED5: LTL-1CHG; LTL1CHG; Mouser Part Number 859-LTL-1CHG
Q1: 2N7002; SOT-23; Part Number 2N7002
R1, R2, R3, R7, R9, R11, R30: 100k; R_Axial_DIN0207_L6.3mm_D2.5mm_P10.16mm_Horizontal; Part Number MCF 0.25W 100K
R4, R5, R6: 1k; R_Axial_DIN0207_L6.3mm_D2.5mm_P10.16mm_Horizontal; Part Number MCF 0.25W 1K
R8, R10, R12: 5.1k; R_Axial_DIN0207_L6.3mm_D2.5mm_P10.16mm_Horizontal; Part Number MCF 0.25W 5K1
R13, R14, R15, R16, R17, R18, R22, R25, R26, R27, R28, R29: 10k; R_Axial_DIN0207_L6.3mm_D2.5mm_P10.16mm_Horizontal; Part Number MCF 0.25W 10K
R20, R24: 39k; R_Axial_DIN0207_L6.3mm_D2.5mm_P10.16mm_Horizontal; Part Number MCF 0.25W 39K
R23: 15k; R_Axial_DIN0207_L6.3mm_D2.5mm_P10.16mm_Horizontal; Part Number MCF 0.25W 15K
R31: 10k; R_0805_2012Metric; Part Number RC0805FR-0710KL
R32: 100k; R_0805_2012Metric; Part Number RC0805FR-07100KL
R33, R35: 1k; R_0805_2012Metric; Part Number RC0805FR-071KL
R34, R36: 18k; R_0805_2012Metric; Part Number RC0805FR-0718KL
RV1, RV2, RV3: 10k potentiometer; Potentiometer_Bourns_3296W_Vertical; Part Number 3296W-1-103LF
TP1, TP2, TP3, TP4, TP5, TP6: TestPoint; TestPoint_Loop_D2.60mm_Drill1.6mm_Beaded; Part Number 36-5006-ND
U4: LM7805MPX/NOPB; SOT-223-3_TabPin2; Part Number LM7805MPX/NOPB
U5, U19: LM339N; DIP794W53P254L1930H508Q14N; Part Number LM339N
U6, U20, U21: SN74AHC1G02DBVR; SOT-23-5; Part Number SN74AHC1G02DBVR
U9: SN74LVC1G04DBVT; SOT-23-5; Part Number SN74LVC1G04DBVT
U18: SN74AHCT1G08DBVR; SOT-23-5; Part Number SN74AHCT1G08DBVR
U22, U23: LM393; SOIC-8_3.9x4.9mm_P1.27mm; Part Number LM393DR

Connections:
+5V: C5.1, C6.2, C8.2, C9.2, C13.1, C14.1, LED1.1 (A), LED2.1 (A), LED3.1 (A), LED4.1 (A), LED5.1 (A), R7.2, R9.2, R11.2, R13.2, R14.2, R15.2, R22.2, R24.2, R26.2, R27.1, R31.1, R33.1, R35.1, RV1.1, RV2.1, RV3.1, U4.3 (VO), U6.5 (VCC), U9.5 (VCC), U18.5 (VCC), U20.5 (VCC), U21.5 (VCC)
/500ms: C10.1, R20.2, U5.10 (-)
/BSPD_TRIP: U9.4, U21.2
/FAULT_F: C15.1, R32.2, U22.5 (+)
/FAULT_N: R31.2, R32.1, U5.1, U19.1, U19.14, U22.1, U23.1, U23.7
/LATCH_Q: U5.8 (-), U20.4, U21.1
/LATCH_QN: U20.1, U21.4
/OVR_REF_BRK: R35.2, R36.1, U23.3 (+), U23.5 (+)
/OVR_REF_CUR: R33.2, R34.1, U22.3 (+)
/POR: C13.2, D10.1 (K), R30.1, U20.2
/REF_1V0: R24.1, R25.2, U5.9 (+), U22.6 (-)
/SENS_CUR: R4.1, TP1.1, U5.4 (-), U5.7 (+), U22.2 (-)
/SENS_FRONT: R5.1, TP2.1, U19.4 (-), U19.7 (+), U23.2 (-)
/SENS_REAR: R6.1, TP3.1, U19.9 (+), U19.10 (-), U23.6 (-)
/TRIP_REQ_N: R26.1, R28.2, U5.13, U9.2, U22.7
BRAKE_SENSOR_FRONT: J1.1, R2.2, R5.2
BRAKE_SENSOR_REAR: J1.2, R3.2, R6.2
BSPD_Shutdown+: J2.1, K1.3
BSPD_Shutdown-: J2.2, K1.2
CURRENT_SENSOR: J1.3, R1.2, R4.2
GLV+: C4.1, C7.2, C12.2, C16.1, D9.1 (K), J3.1, K1.1, U4.1 (VI), U5.3 (V+), U19.3 (V+), U22.8 (V+), U23.8 (V+)
GLV-: C4.2, C5.2, C6.1, C7.1, C8.1, C9.1, C10.2, C12.1, C14.2, C15.2, C16.2, D10.2 (A), J3.2, Q1.2 (S), R1.1, R2.1, R3.1, R8.1, R10.1, R12.1, R23.1, R25.1, R30.2, R34.2, R36.2, RV1.3, RV2.3, RV3.3, U4.2 (GND), U5.12 (V-), U6.3 (GND), U9.3 (GND), U18.3 (GND), U19.12 (V-), U20.3 (GND), U21.3 (GND), U22.4 (V-), U23.4 (V-)
unnamed: D9.2 (A), K1.5, Q1.3 (D)
unnamed: LED1.2 (K), R16.2
unnamed: LED2.2 (K), R17.1
unnamed: LED3.2 (K), R18.1
unnamed: LED4.2 (K), R28.1
unnamed: LED5.2 (K), R29.1
unnamed: Q1.1 (G), R27.2, R29.2, U5.14
unnamed: R13.1, R16.1, U5.2, U6.1
unnamed: R14.1, R17.2, U18.1, U19.2
unnamed: R15.1, R18.2, U18.2, U19.13
unnamed: R20.1, U6.4
unnamed: RV1.2, TP4.1, U5.5 (+)
unnamed: R7.1, R8.2, U5.6 (-)
unnamed: R22.1, R23.2, U5.11 (+)
unnamed: U6.2, U18.4
unnamed: RV2.2, TP5.1, U19.5 (+)
unnamed: R9.1, R10.2, U19.6 (-)
unnamed: RV3.2, TP6.1, U19.11 (+)
unnamed: R11.1, R12.2, U19.8 (-)

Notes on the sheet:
Current sensor potentiometer should be set to whatever sensor outputs at 16A V_threshold = 2.5 V + (15.9 A × 0.010 V/A) ≈ 2.66 V or better: TP4 = zero-current sensor voltage + 0.16 V
NOR Logic
>5kW Power
Hard Braking
M7139-500PG-P00000 Pressure Sensor
Minimum Voltage
AND GATE
ALl LEDs are off when BSPD is OK
Orion BMS Current Sesor
Implausibility Timer Circuit
Current Sensor
Shutdown
Below 0.24 V or above 4.74 V = sensor fault (trips the BSPD) 20 bar corresponds 2.8V 25 bar corresponds to 3.36V 30 bar correspons to 3.93v
Brake Pressure Sensor FRONT
BSPD is closed when NOT( hard braking AND too much power for >500 ms )
Brake Pressure Sensor REAR
5V LDO Regulator
Latch Circuit (fault latched until LVMS power cycle)
LED5 OFF = relay closed LED5 ON = relay open
Latch: fault >500ms -> BSPD_TRIP high -> LATCH_Q high -> U5D out low -> Q1 off -> relay open. Stays latched until LVMS power cycle (T11.6.1). POR (C13/R30/D10) clears latch at power-up. Replaces 10s RC self-reset: hold time was 6.8-13.6s vs 10s minimum.
Sensor Fault Detection (T11.9.2): a sensor reading below 0.24 V (open circuit, short to GND) or above 4.74 V (short to supply) pulls FAULT_N low (under-range: U5B, U19B, U19D; over-range: U22A, U23A, U23B). R32/C15 debounce it (~0.17 s), then U22B pulls TRIP_REQ_N low -> U9 -> BSPD_TRIP -> latch (u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

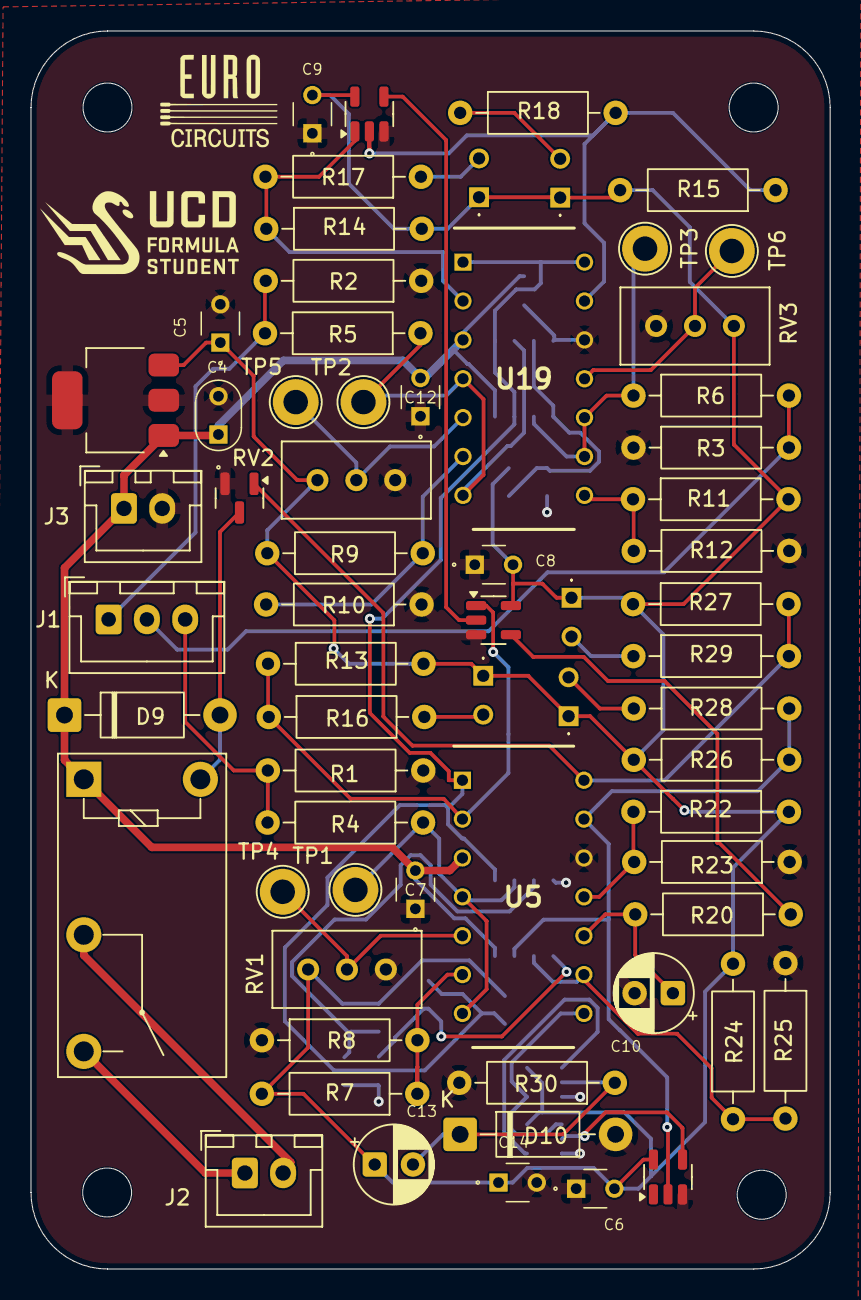
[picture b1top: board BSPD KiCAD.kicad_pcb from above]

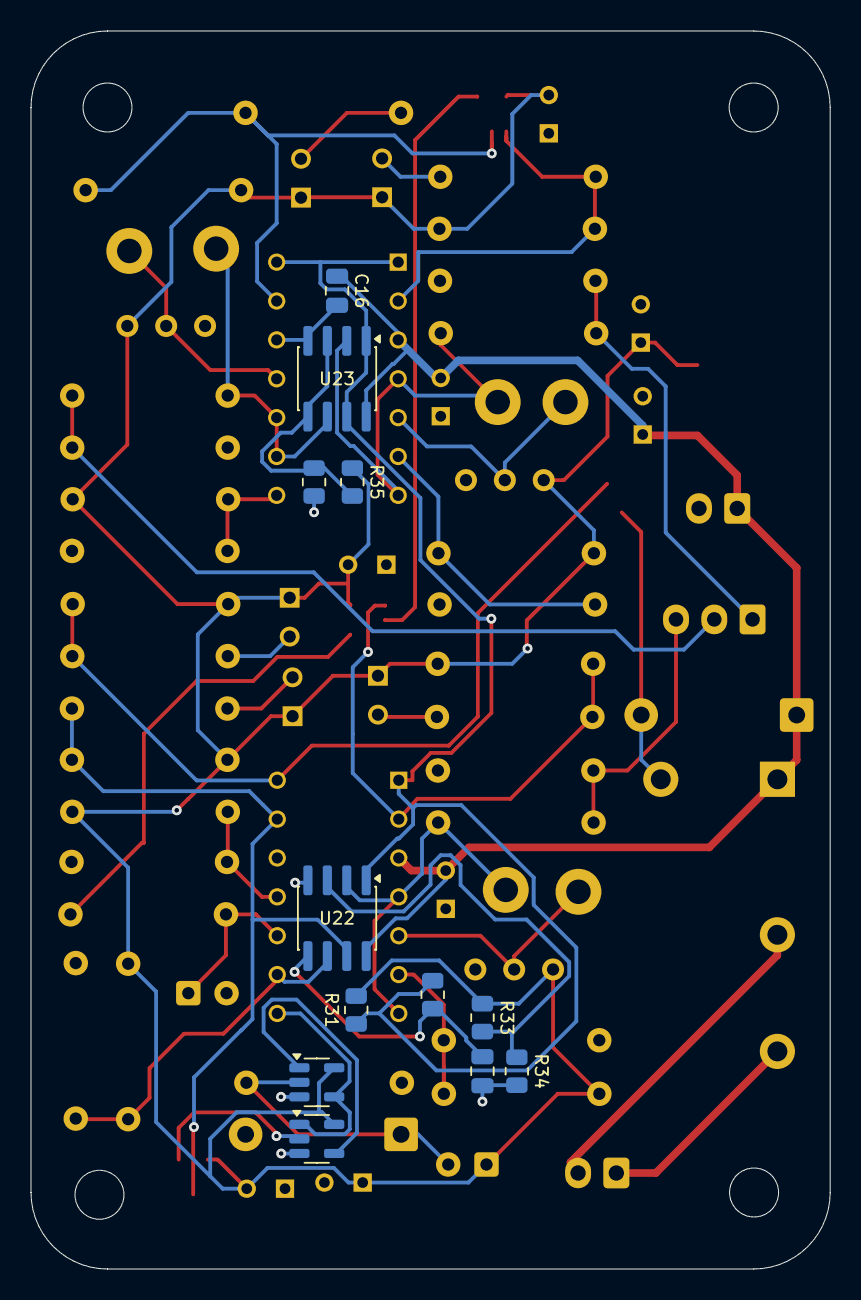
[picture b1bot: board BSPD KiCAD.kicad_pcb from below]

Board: 2 copper layers, 52.2 x 80.9 mm, 81 parts (12 on the bottom side), 41 nets.

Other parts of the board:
H1, H2, H3, H4: MountingHole_3.2mm_M3

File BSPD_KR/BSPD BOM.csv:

"Reference","Value","Part Number","Datasheet","Footprint","Qty","DNP"
"C4","0.22uF","FA14X7R1H224KNU00","https://www.farnell.com/datasheets/2923220.pdf","Kicad_Libraries:FA14X7R1H224KNU00","1",""
"C5,C6,C7,C8,C9,C12,C14","0.1uF","FA18X7R1H104KNU00","https://www.farnell.com/datasheets/2923220.pdf","Kicad_Libraries:FA18X7R1H104KNU00","7",""
"C10,C13","10uF","ECE-A1EKA100I","https://industrial.panasonic.com/cdbs/www-data/pdf/RDF0000/A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","Capacitor_THT:CP_Radial_D5.0mm_P2.50mm","2",""
"C15","1uF","CL21B105KBFNNNE","","Capacitor_SMD:C_0805_2012Metric","1",""
"C16","0.1uF","CL21B104KBCNNNC","","Capacitor_SMD:C_0805_2012Metric","1",""
"D9","1N4001","1N4001","http://www.vishay.com/docs/88503/1n4001.pdf","Diode_THT:D_DO-41_SOD81_P10.16mm_Horizontal","1",""
"D10","1N4148","1N4148","","Diode_THT:D_DO-41_SOD81_P10.16mm_Horizontal","1",""
"J1","Conn_01x03","B3B-XH-A","https://www.jst-mfg.com/product/pdf/eng/eXH.pdf","Connector_JST:JST_XH_B3B-XH-A_1x03_P2.50mm_Vertical","1",""
"J2,J3","Conn_01x02","B2B-XH-A ","https://www.jst-mfg.com/product/pdf/eng/eXH.pdf","Connector_JST:JST_XH_B2B-XH-A_1x02_P2.50mm_Vertical","2",""
"K1","G5Q-1A4-DC12","G5Q-1A4-DC12","https://www.mouser.ie/datasheet/2/307/J155_E1-3439950.pdf","Relay_THT:Relay_SPST_Omron-G5Q-1A","1",""
"LED1,LED2,LED3,LED4,LED5","LTL-1CHG","LTL-1CHG","https://media.digikey.com/pdf/Data%20Sheets/Lite-On%20PDFs/L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","Kicad_Libraries:LTL1CHG","5",""
"Q1","2N7002","2N7002","https://www.onsemi.com/pub/Collateral/NDS7002A-D.PDF","Package_TO_SOT_SMD:SOT-23","1",""
"R1,R2,R3,R7,R9,R11,R30","100k","MCF 0.25W 100K","https://www.farnell.com/datasheets/3436052.pdf?_gl=1*10s1yq3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","Resistor_THT:R_Axial_DIN0207_L6.3mm_D2.5mm_P10.16mm_Horizontal","7",""
"R4,R5,R6","1k","MCF 0.25W 1K","https://www.farnell.com/datasheets/3436052.pdf?_gl=1*1pxxutc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","Resistor_THT:R_Axial_DIN0207_L6.3mm_D2.5mm_P10.16mm_Horizontal","3",""
"R8,R10,R12","5.1k","MCF 0.25W 5K1","https://www.farnell.com/datasheets/3436052.pdf?_gl=1*j4k0i6*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","Resistor_THT:R_Axial_DIN0207_L6.3mm_D2.5mm_P10.16mm_Horizontal","3",""
"R13,R14,R15,R16,R17,R18,R22,R25,R26,R27,R28,R29","10k","MCF 0.25W 10K","https://www.farnell.com/datasheets/3436052.pdf?_gl=1*j4k0i6*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","Resistor_THT:R_Axial_DIN0207_L6.3mm_D2.5mm_P10.16mm_Horizontal","12",""
"R20,R24","39k","MCF 0.25W 39K","http://www.farnell.com/datasheets/3436052.pdf?_gl=1*shqhxd*_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,https://www.farnell.com/datasheets/3436052.pdf?_gl=1*6igt67*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","Resistor_THT:R_Axial_DIN0207_L6.3mm_D2.5mm_P10.16mm_Horizontal","2",""
"R23","15k","MCF 0.25W 15K","https://www.farnell.com/datasheets/3436052.pdf?_gl=1*2i638p*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","Resistor_THT:R_Axial_DIN0207_L6.3mm_D2.5mm_P10.16mm_Horizontal","1",""
"R31","10k","RC0805FR-0710KL","","Resistor_SMD:R_0805_2012Metric","1",""
"R32","100k","RC0805FR-07100KL","","Resistor_SMD:R_0805_2012Metric","1",""
"R33,R35","1k","RC0805FR-071KL","","Resistor_SMD:R_0805_2012Metric","2",""
"R34,R36","18k","RC0805FR-0718KL","","Resistor_SMD:R_0805_2012Metric","2",""
"RV1,RV2,RV3","10k potentiometer","3296W-1-103LF","https://www.mouser.ie/datasheet/2/54/3296-776415.pdf","Potentiometer_THT:Potentiometer_Bourns_3296W_Vertical","3",""
"TP1,TP2,TP3,TP4,TP5,TP6","TestPoint","36-5006-ND","https://www.keyelco.com/userAssets/file/M65p56.pdf","TestPoint:TestPoint_Loop_D2.60mm_Drill1.6mm_Beaded","6",""
"U4","LM7805MPX/NOPB","LM7805MPX/NOPB","https://www.ti.com/lit/gpn/lm7800","Package_TO_SOT_SMD:SOT-223-3_TabPin2","1",""
"U5,U19","LM339N","LM339N","https://www.ti.com/lit/gpn/lm339","Kicad_Libraries:DIP794W53P254L1930H508Q14N","2",""
"U6,U20,U21","SN74AHC1G02DBVR","SN74AHC1G02DBVR","https://www.ti.com/lit/ds/symlink/sn74ahc1g02.pdf,https://www.ti.com/lit/ds/symlink/sn74ahc1g02.pdf?ts=1738520903275","Package_TO_SOT_SMD:SOT-23-5","3",""
"U9","SN74LVC1G04DBVT","SN74LVC1G04DBVT","https://www.ti.com/lit/gpn/sn74lvc1g04","Package_TO_SOT_SMD:SOT-23-5","1",""
"U18","SN74AHCT1G08DBVR","SN74AHCT1G08DBVR","https://www.ti.com/lit/gpn/sn74ahct1g08","Package_TO_SOT_SMD:SOT-23-5","1",""
"U22,U23","LM393","LM393DR","https://www.ti.com/lit/ds/symlink/lm393.pdf","Package_SO:SOIC-8_3.9x4.9mm_P1.27mm","2",""

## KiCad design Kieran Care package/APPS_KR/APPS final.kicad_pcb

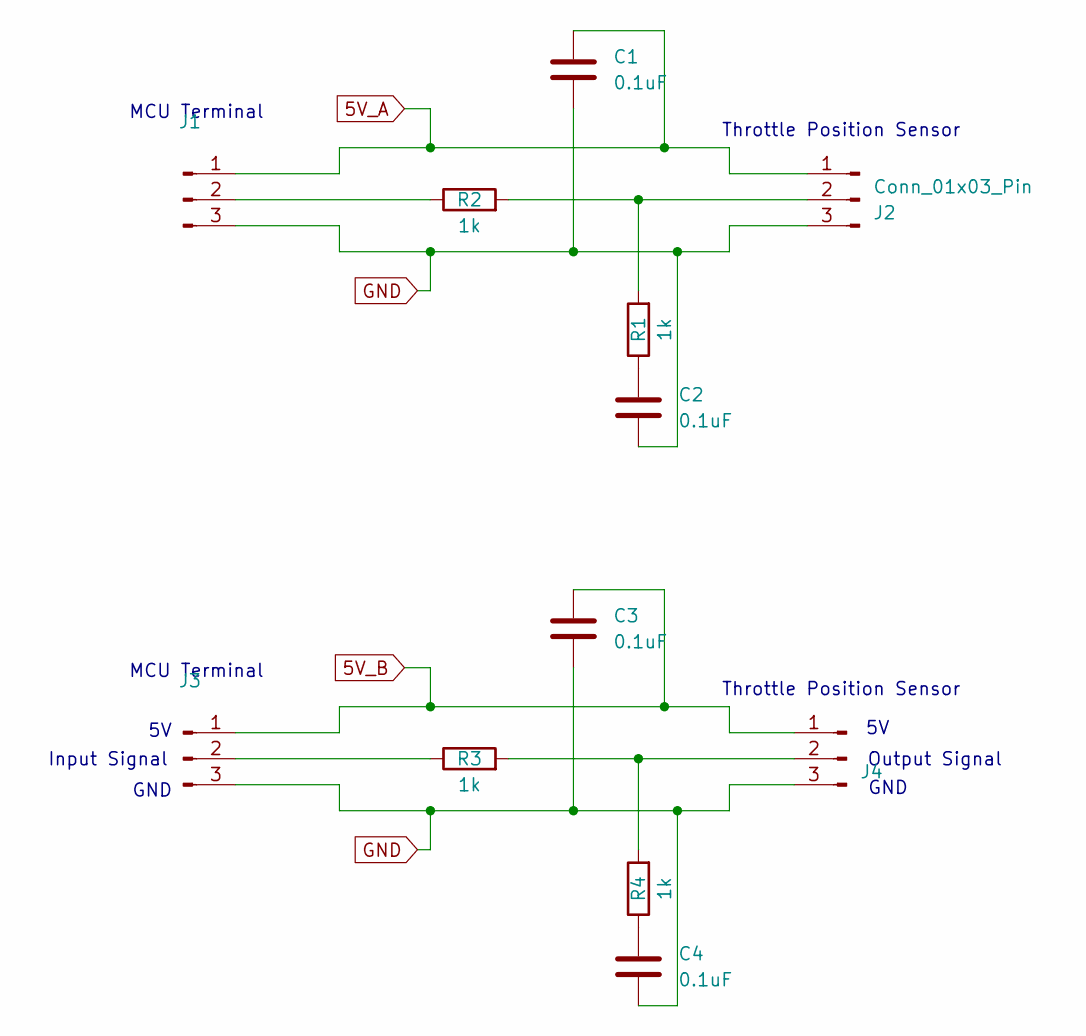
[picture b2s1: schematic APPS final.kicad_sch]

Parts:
C1, C2, C3, C4: 0.1uF; FA18X7R1H104KNU00; Part Number FA18X7R1H104KNU00
J1, J2, J3, J4: Conn_01x03_Pin; JST_XH_B3B-XH-A_1x03_P2.50mm_Vertical; Part Number B3B-XH-A
R1, R2, R3, R4: 1k; R_Axial_DIN0207_L6.3mm_D2.5mm_P10.16mm_Horizontal; Part Number MCF 0.25W 1K

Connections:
5V_A: C1.1, J1.1, J2.1
5V_B: C3.1, J3.1, J4.1
GND: C1.2, C2.2, C3.2, C4.2, J1.3, J2.3, J3.3, J4.3
unnamed: C2.1, R1.1
unnamed: C4.1, R4.1
unnamed: J1.2, R2.1
unnamed: J2.2, R1.2, R2.2
unnamed: J3.2, R3.1
unnamed: J4.2, R3.2, R4.2

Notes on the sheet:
Throttle Position Sensor
MCU Terminal
Output Signal
GND
Input Signal

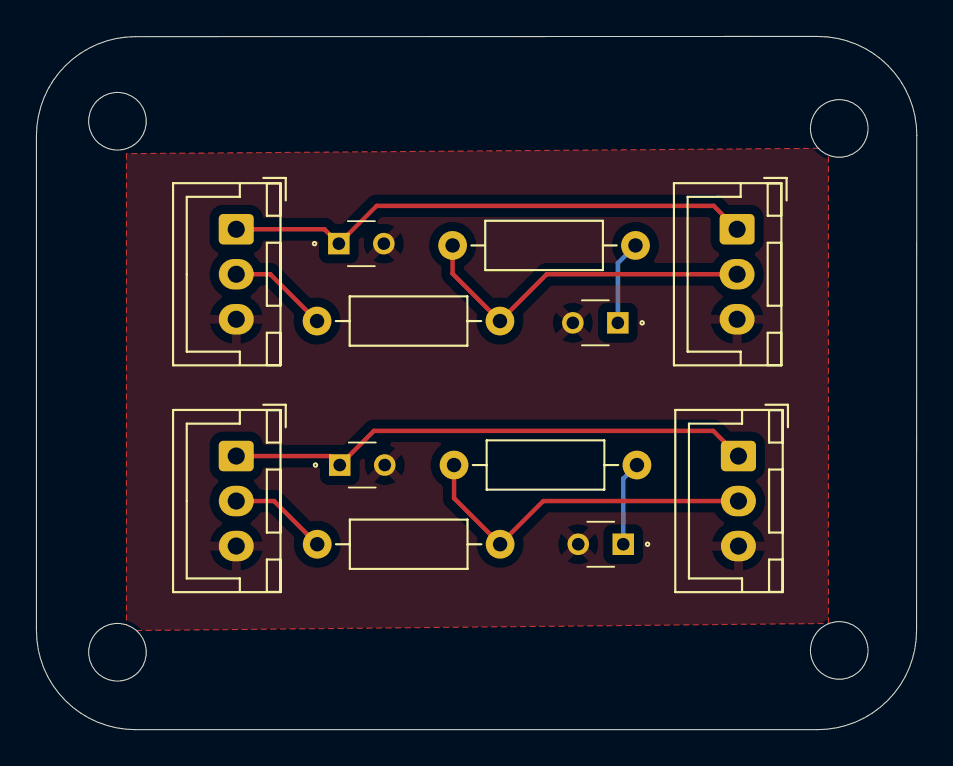
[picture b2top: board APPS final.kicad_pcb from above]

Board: 2 copper layers, 48.9 x 38.5 mm, 12 parts (0 on the bottom side), 9 nets.
